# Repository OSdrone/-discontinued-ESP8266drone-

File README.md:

# ESP8266drone
Robot Controller based on ESP8266 running FreeRTOS

The main idea is to design and develop the controller of an autonomus robot, like a quadcopter.

The ESP8266Drone is based on the ESP8266 IC, which includes a microprocessor and a Wifi link both in the same chip.

The desing has two parts:

  -Hardware : PCB support for ICs (Sensors and microprocessor) and the electronic necessary to control the brush motors.
  
  -Software : The ESP8266 firmware to sense, control and communicate with the App. It's developed using FreeRTOS version. This part also includes an Android Application that allows to pilot and receive telemetry from the ESP8266Drone.

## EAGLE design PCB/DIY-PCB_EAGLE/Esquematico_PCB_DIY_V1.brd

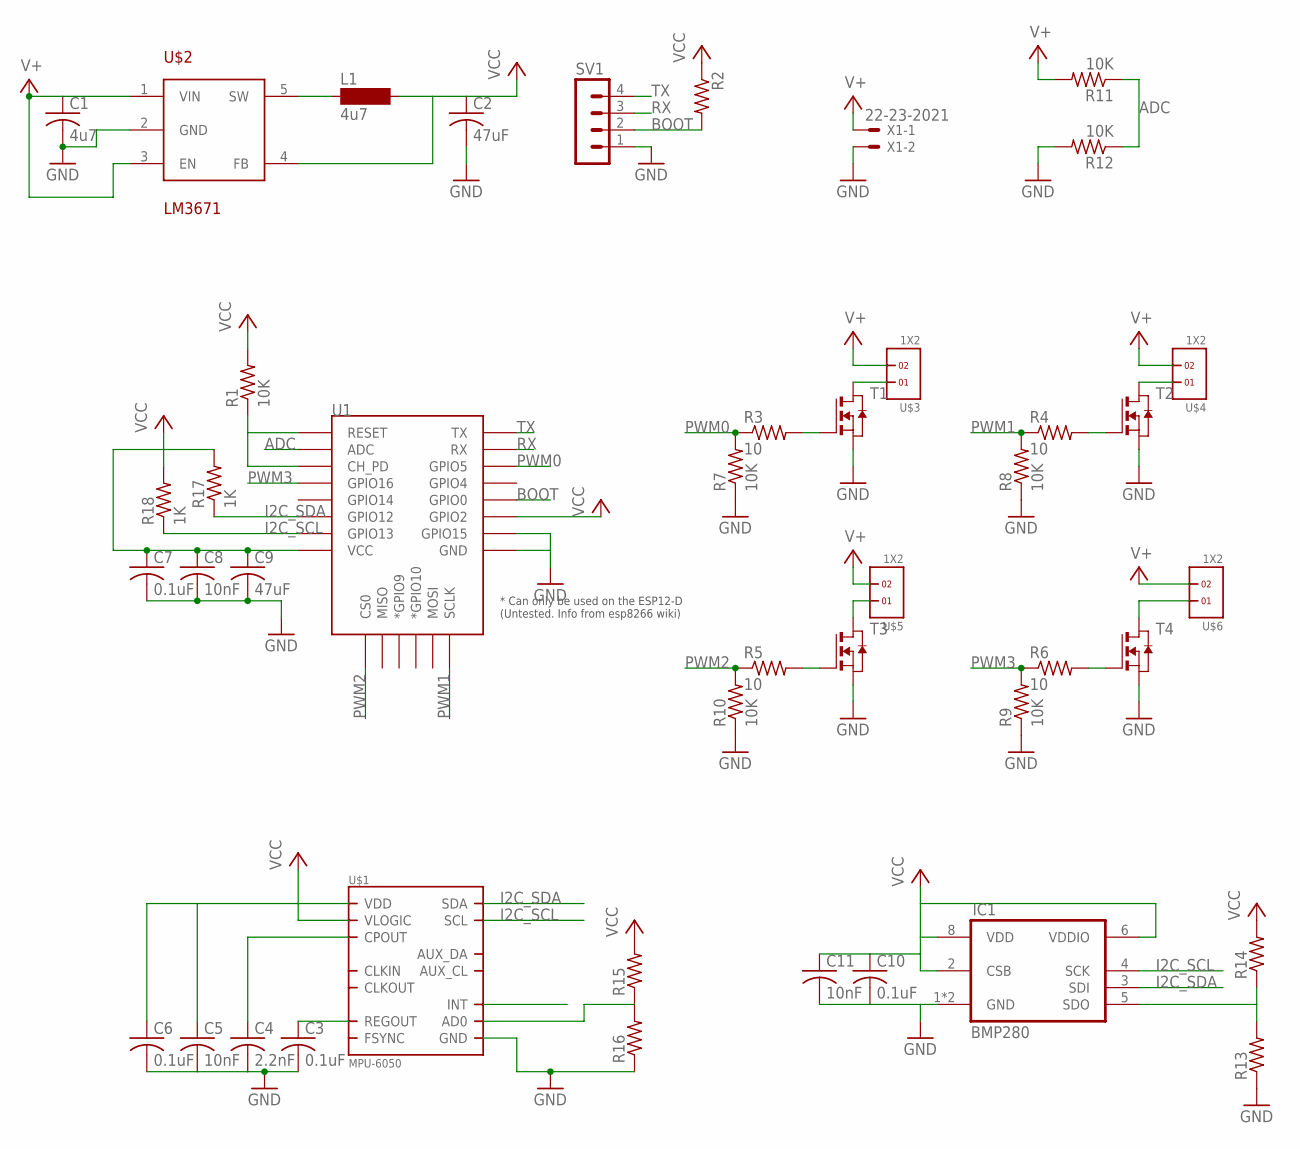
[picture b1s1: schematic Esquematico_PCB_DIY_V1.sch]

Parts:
C1: 4u7; C0805K
C2, C9: 47uF; C0805K
C3, C6, C7, C10: 0.1uF; C0805K
C4: 2.2nF; C0805K
C5, C8, C11: 10nF; C0805K
IC1: BMP280
L1: 4u7; MS85
R1, R7, R8, R9, R10, R11, R12: 10K; R0805
R2, R13, R14, R15, R16: R-US_R0805; R0805
R3, R4, R5, R6: 10; R0805
R17, R18: 1K; R0805
SV1: MA04-1
T1, T2, T3, T4: NMOSSOT23; SOT-23
U1: ESP12ESMD; ESP12E-SMD
U$1: MPU-6050; QFN.24.4X4
U$2: LM3671; SOT23-5
U$3, U$4, U$5, U$6: 1X2
X1: 22-23-2021

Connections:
ADC: R11.1, R12.1, U1.ADC
BOOT: R2.2, SV1.2, U1.GPIO0
GND: C1.2, C2.2, C3.2, C4.2, C5.2, C6.2, C7.2, C8.2, C9.2, C10.2, C11.2, IC1.1 (GND), IC1.7 (GND), R7.1, R8.1, R9.1, R10.1, R12.2, R13.1, R16.1, SV1.1, T1.2 (S), T2.2 (S), T3.2 (S), T4.2 (S), U1.GND, U1.GPIO15, U$1.18 (GND), U$2.2 (GND), X1.2
I2C_SCL: IC1.4 (SCK), R18.1, U1.GPIO13, U$1.23 (SCL)
I2C_SDA: IC1.3 (SDI), R17.1, U1.GPIO12, U$1.24 (SDA)
unnamed: R1.1, U1.CH_PD, U1.RESET
unnamed: R3.2, T1.3 (G)
unnamed: L1.1, U$2.5 (SW)
unnamed: R4.2, T2.3 (G)
unnamed: R5.2, T3.3 (G)
unnamed: R6.2, T4.3 (G)
unnamed: IC1.5 (SDO), R13.2, R14.1
unnamed: R15.1, R16.2, U$1.9 (AD0)
unnamed: T3.1 (D), U$5.1
unnamed: C3.1, U$1.10 (REGOUT)
unnamed: C4.1, U$1.20 (CPOUT)
unnamed: T4.1 (D), U$6.1
unnamed: T2.1 (D), U$4.1
unnamed: T1.1 (D), U$3.1
PWM0: R3.1, R7.2, U1.GPIO5
PWM1: R4.1, R8.2, U1.SCLK
PWM2: R5.1, R10.2, U1.CS0
PWM3: R6.1, R9.2, U1.GPIO16
RX: SV1.3, U1.RXD0 (RX)
TX: SV1.4, U1.TXD0 (TX)
V+: C1.1, R11.2, U$2.1 (VIN), U$2.3 (EN), U$3.2, U$4.2, U$5.2, U$6.2, X1.1
VCC: C2.1, C5.1, C6.1, C7.1, C8.1, C9.1, C10.1, C11.1, IC1.2 (CSB), IC1.6 (VDDIO), IC1.8 (VDD), L1.2, R1.2, R2.1, R14.2, R15.2, R17.2, R18.2, U1.GPIO2, U1.VCC, U$1.8 (VLOGIC), U$1.13 (VDD), U$2.4 (FB)

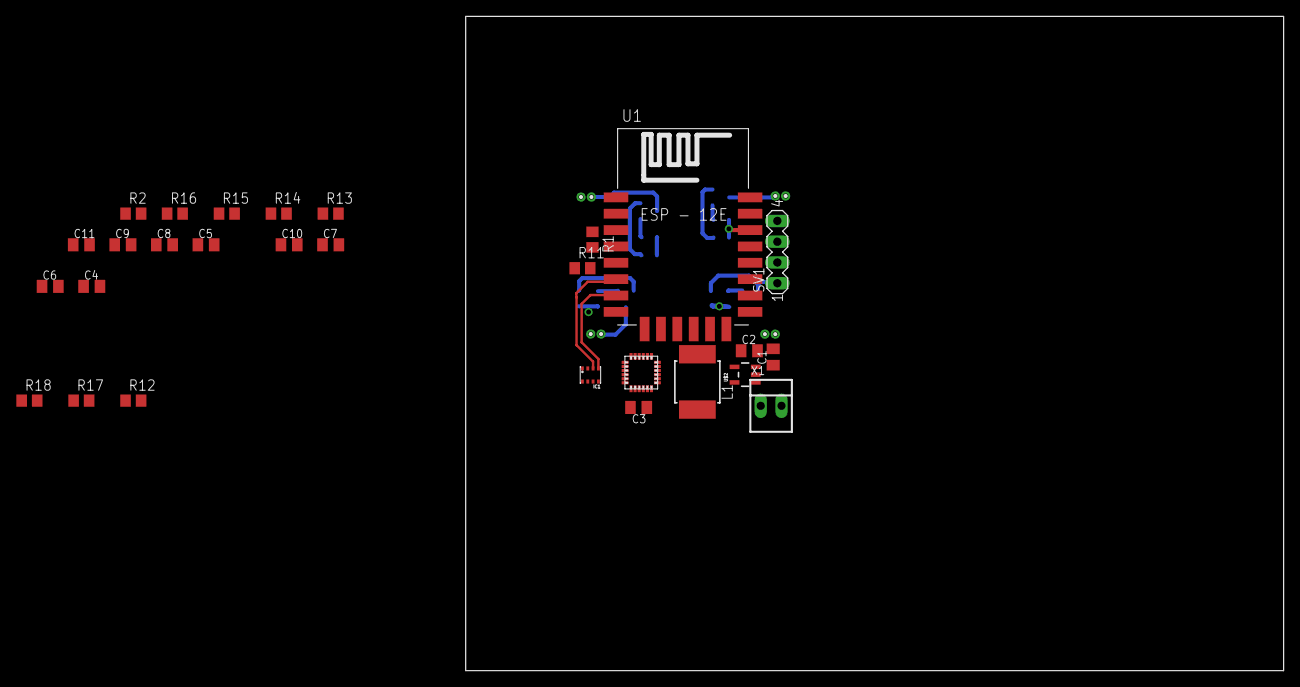
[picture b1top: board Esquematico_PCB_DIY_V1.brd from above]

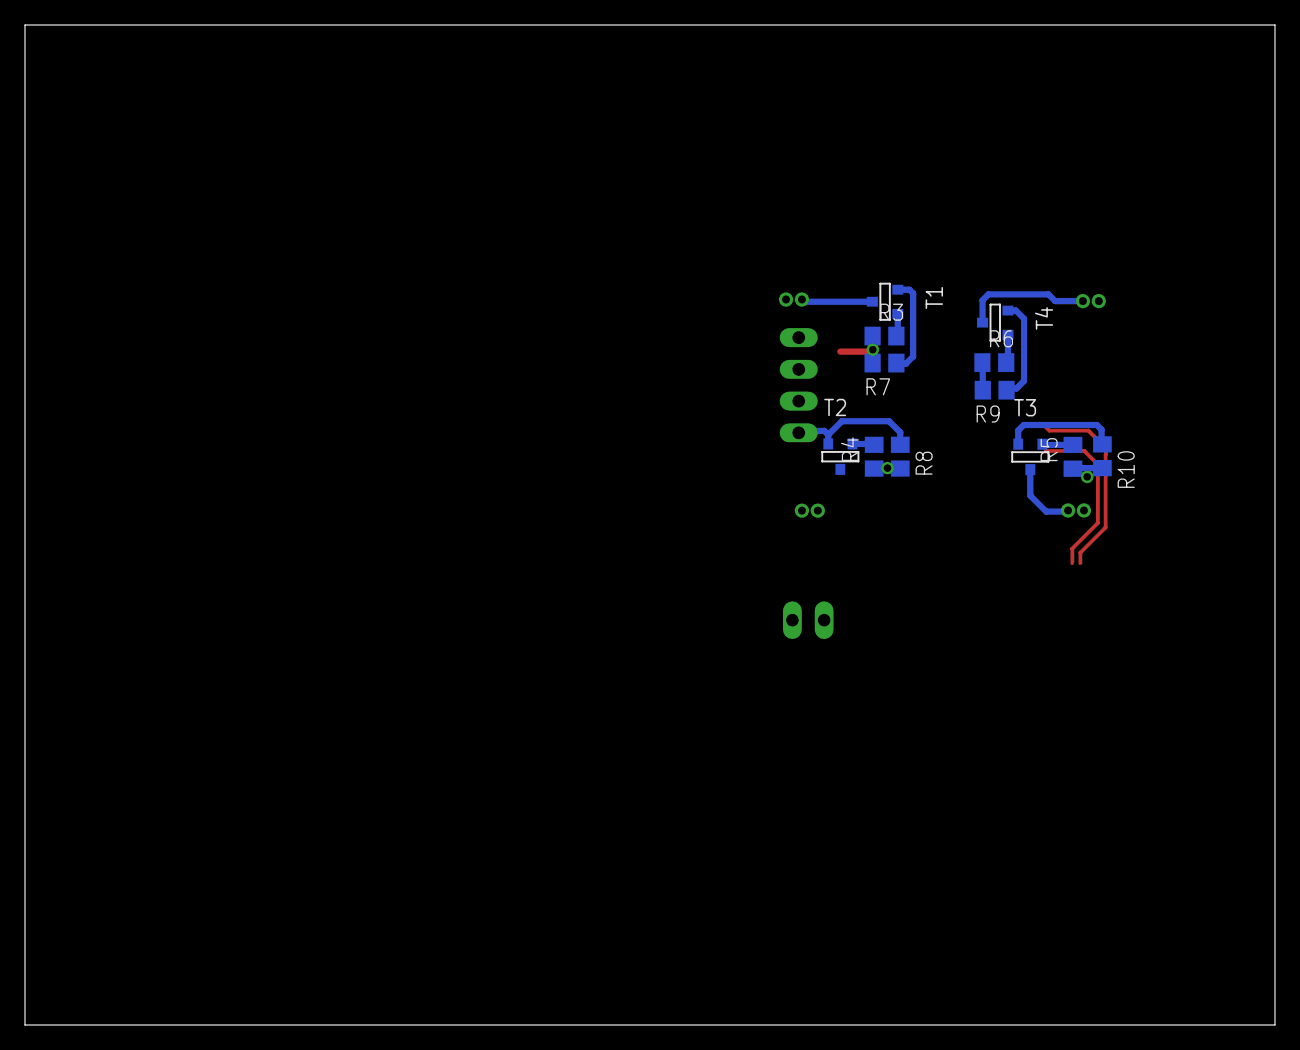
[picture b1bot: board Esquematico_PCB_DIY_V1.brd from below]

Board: 2 copper layers, 100.0 x 80.0 mm, 44 parts (12 on the bottom side), 27 nets.

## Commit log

2016-08-19 Rename README.md to README_explain.md
2016-08-19 Revert "Update README.md"
    This reverts commit 02e426dec0176a8a3c23f60d55354bcc8242775f.
2016-08-19 Revert "Add files via upload"
    This reverts commit b33166fbe6dccfa26cb3ae77c87bb12e3c1e3be3.
2016-08-19 Version Inicial del proyecto
2016-08-19 Añadido descripcion funcionamiento
2016-08-19 Añadido Carpeta Programacion
2016-08-19 Añadido Altium
2016-08-20 Dmp Invesense
2016-08-20 PCB_EAGLE CHANGES
2016-08-21 Esquematico
2016-08-21 Esquematico Final
2016-08-22 Drone ESP ALtium
2016-08-22 Alimentacion Conmutada
    Altium Version
2016-08-22 ESP Conmutada
2016-08-22 ESP8266 Version 1
2016-08-29 Programacion
2016-09-06 WiFi
    WiFi library, and user_init change needed
